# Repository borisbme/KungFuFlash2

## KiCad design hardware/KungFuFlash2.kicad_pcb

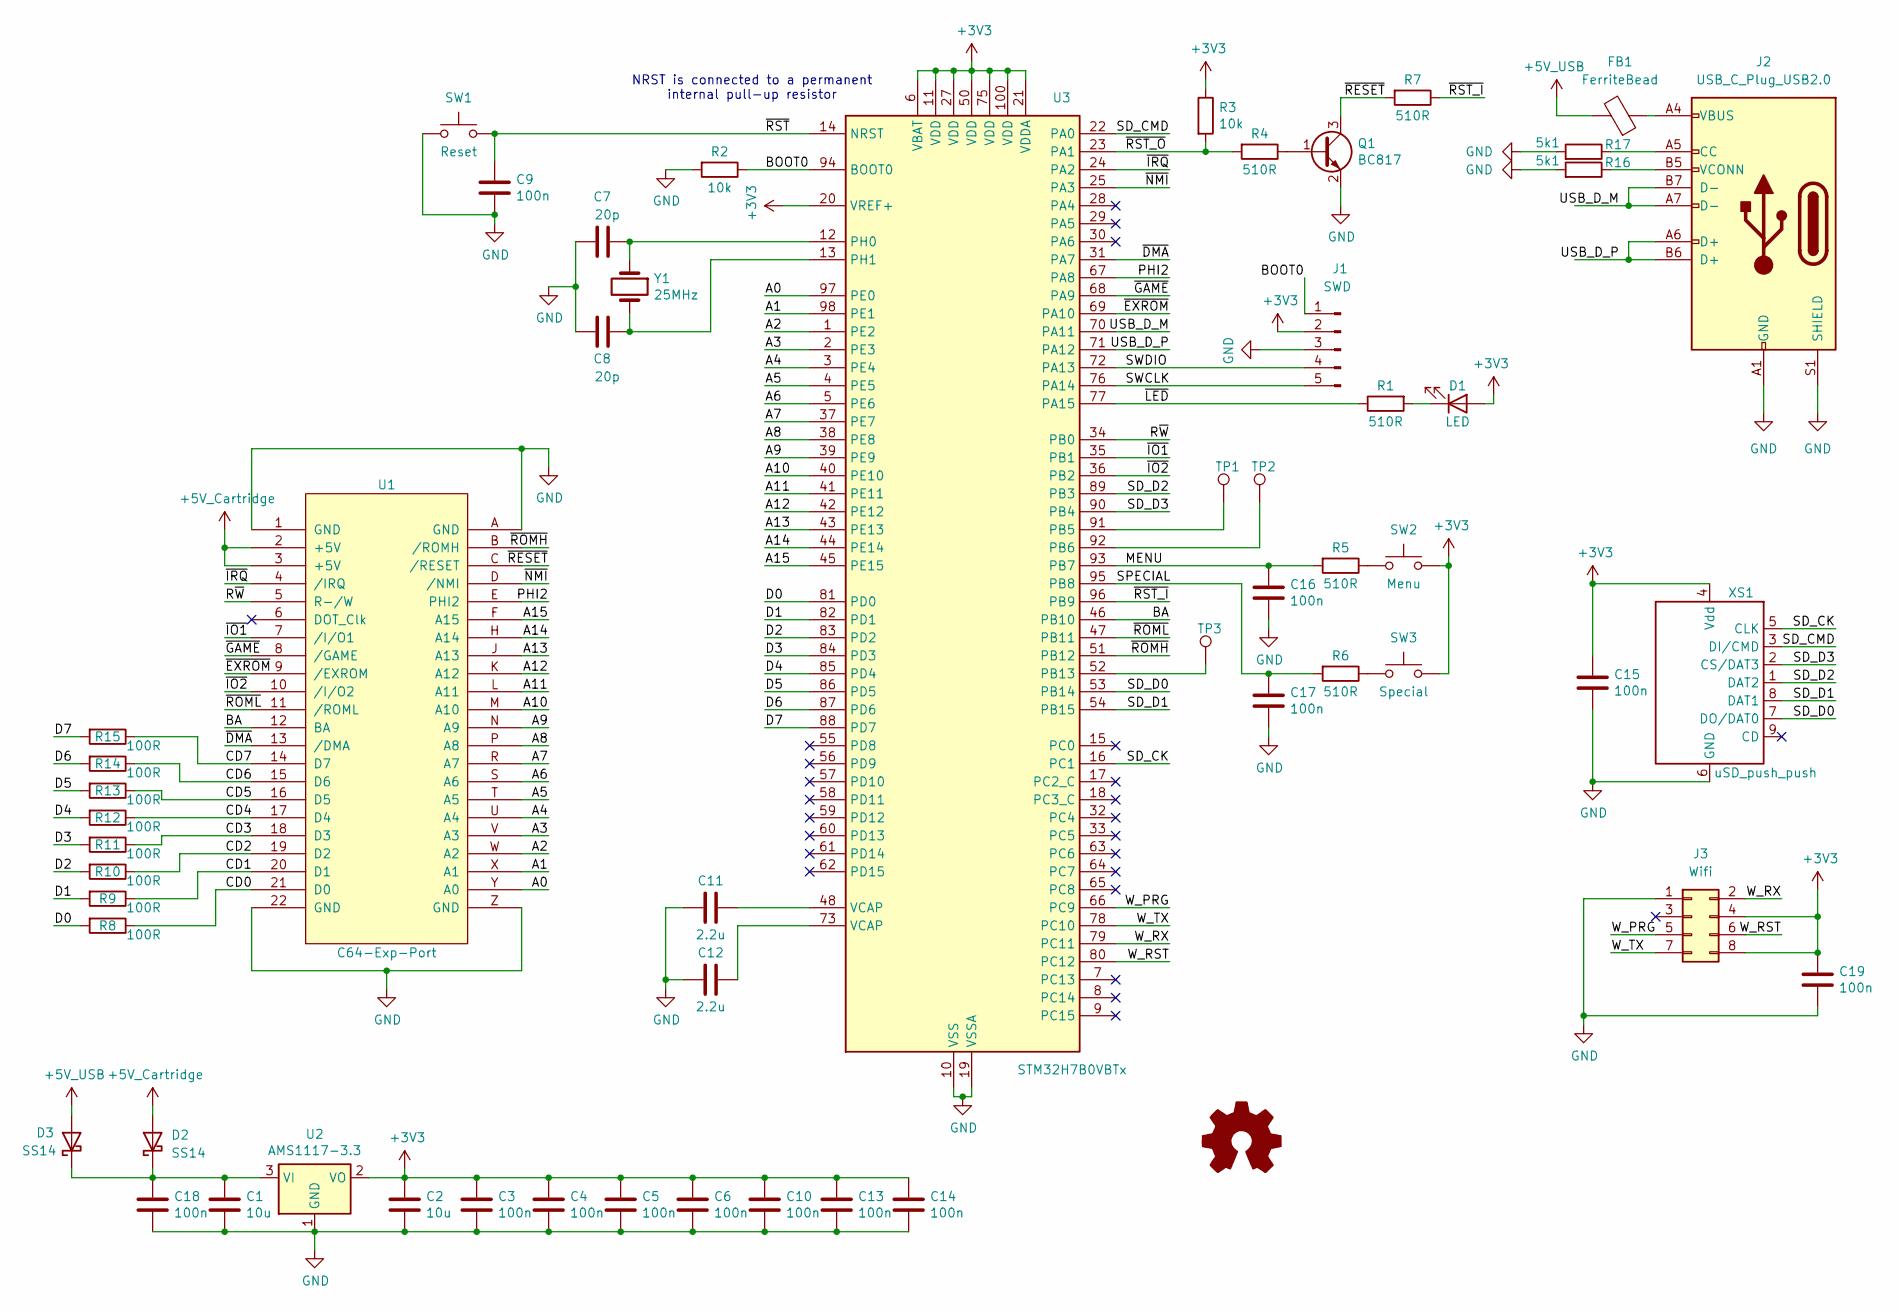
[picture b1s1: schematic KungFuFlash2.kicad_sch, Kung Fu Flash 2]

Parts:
C1, C2: 10u; C_0805_2012Metric_Pad1.18x1.45mm_HandSolder; LCSC C19702
C3, C4, C5, C6, C9, C10, C13, C14, C15, C16, C17, C18, C19: 100n; C_0603_1608Metric_Pad1.08x0.95mm_HandSolder; LCSC C38898
C7, C8: 20p; C_0603_1608Metric_Pad1.08x0.95mm_HandSolder; LCSC C105621
C11, C12: 2.2u; C_0805_2012Metric_Pad1.18x1.45mm_HandSolder; LCSC C19110
D1: LED; LED_0805_2012Metric_Pad1.15x1.40mm_HandSolder; LCSC C84256
D2, D3: SS14; D_SMA_Handsoldering; LCSC C2480
FB1: FerriteBead; L_0805_2012Metric_Pad1.15x1.40mm_HandSolder; LCSC C1015
J1: SWD; PinHeader_1x05_P2.54mm_Vertical; LCSC C492404
J2: USB_C_Plug_USB2.0; USB_C_Receptacle_GCT_USB4105-xx-A_16P_TopMnt_Horizontal; LCSC C165948
J3: Wifi; PinSocket_2x04_P2.54mm_Vertical; LCSC C18723055
Q1: BC817; SOT-23; LCSC C52801
R1, R4, R5, R6, R7: 510R; R_0805_2012Metric_Pad1.20x1.40mm_HandSolder; LCSC C17734
R2, R3: 10k; R_0805_2012Metric_Pad1.20x1.40mm_HandSolder; LCSC C17414
R8, R9, R10, R11, R12, R13, R14, R15: 100R; R_0805_2012Metric_Pad1.20x1.40mm_HandSolder; LCSC C17408
R16, R17: 5k1; R_0805_2012Metric_Pad1.20x1.40mm_HandSolder; LCSC C27834
SW1: Reset; SW_PUSH_6mm_H8mm; LCSC C285486
SW2: Menu; SW_PUSH_6mm_H8mm; LCSC C285486
SW3: Special; SW_PUSH_6mm_H8mm; LCSC C285486
TP1, TP2, TP3: TestPoint_Pad_1.0x1.0mm
U1: C64-Exp-Port; C64-Cart
U2: AMS1117-3.3; SOT-223-3_TabPin2; LCSC C347222
U3: STM32H7B0VBTx; LQFP-100_14x14mm_P0.5mm; LCSC C730227
XS1: uSD_push_push; Conn_uSDcard
Y1: 25MHz; Crystal_SMD_5032-2Pin_5.0x3.2mm; LCSC C251592

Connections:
+3V3: C2.1, C3.1, C4.1, C5.1, C6.1, C10.1, C13.1, C14.1, C15.1, C19.1, D1.2 (A), J1.2, J3.4, J3.8, R3.1, SW2.1, SW3.1, U2.2 (VO), U3.6 (VBAT), U3.11 (VDD), U3.20 (VREF+), U3.21 (VDDA), U3.27 (VDD), U3.50 (VDD), U3.75 (VDD), U3.100 (VDD), XS1.4 (Vdd)
+5V_Cartridge: D2.2 (A), U1.2 (+5V), U1.3 (+5V)
+5V_USB: D3.2 (A), FB1.2
/A0: U1.Y (A0), U3.97 (PE0)
/A1: U1.X (A1), U3.98 (PE1)
/A2: U1.W (A2), U3.1 (PE2)
/A3: U1.V (A3), U3.2 (PE3)
/A4: U1.U (A4), U3.3 (PE4)
/A5: U1.T (A5), U3.4 (PE5)
/A6: U1.S (A6), U3.5 (PE6)
/A7: U1.R (A7), U3.37 (PE7)
/A8: U1.P (A8), U3.38 (PE8)
/A9: U1.N (A9), U3.39 (PE9)
/A10: U1.M (A10), U3.40 (PE10)
/A11: U1.L (A11), U3.41 (PE11)
/A12: U1.K (A12), U3.42 (PE12)
/A13: U1.J (A13), U3.43 (PE13)
/A14: U1.H (A14), U3.44 (PE14)
/A15: U1.F (A15), U3.45 (PE15)
/BA: U1.12 (BA), U3.46 (PB10)
/BOOT0: J1.1, R2.1, U3.94 (BOOT0)
/CD0: R8.1, U1.21 (D0)
/CD1: R9.1, U1.20 (D1)
/CD2: R10.1, U1.19 (D2)
/CD3: R11.1, U1.18 (D3)
/CD4: R12.1, U1.17 (D4)
/CD5: R13.1, U1.16 (D5)
/CD6: R14.1, U1.15 (D6)
/CD7: R15.1, U1.14 (D7)
/D0: R8.2, U3.81 (PD0)
/D1: R9.2, U3.82 (PD1)
/D2: R10.2, U3.83 (PD2)
/D3: R11.2, U3.84 (PD3)
/D4: R12.2, U3.85 (PD4)
/D5: R13.2, U3.86 (PD5)
/D6: R14.2, U3.87 (PD6)
/D7: R15.2, U3.88 (PD7)
/MENU: C16.1, R5.2, U3.93 (PB7)
/PHI2: U1.E (PHI2), U3.67 (PA8)
/R~W: U1.5 (R-/W), U3.34 (PB0)
/SD_CK: U3.16 (PC1), XS1.5 (CLK)
/SD_CMD: U3.22 (PA0), XS1.3 (DI/CMD)
/SD_D0: U3.53 (PB14), XS1.7 (DO/DAT0)
/SD_D1: U3.54 (PB15), XS1.8 (DAT1)
/SD_D2: U3.89 (PB3), XS1.1 (DAT2)
/SD_D3: U3.90 (PB4), XS1.2 (CS/DAT3)
/SPECIAL: C17.1, R6.2, U3.95 (PB8)
/SWCLK: J1.5, U3.76 (PA14)
/SWDIO: J1.4, U3.72 (PA13)
/USB_D_M: J2.A7 (D-), J2.B7 (D-), U3.70 (PA11)
/USB_D_P: J2.A6 (D+), J2.B6 (D+), U3.71 (PA12)
/W_PRG: J3.5, U3.66 (PC9)
/W_RST: J3.6, U3.80 (PC12)
/W_RX: J3.2, U3.79 (PC11)
/W_TX: J3.7, U3.78 (PC10)
/~DMA: U1.13 (/DMA), U3.31 (PA7)
/~EXROM: U1.9 (/EXROM), U3.69 (PA10)
/~GAME: U1.8 (/GAME), U3.68 (PA9)
/~IO1: U1.7 (/I/O1), U3.35 (PB1)
/~IO2: U1.10 (/I/O2), U3.36 (PB2)
/~IRQ: U1.4 (/IRQ), U3.24 (PA2)
/~LED: R1.1, U3.77 (PA15)
/~NMI: U1.D (/NMI), U3.25 (PA3)
/~RESET: Q1.3 (C), R7.2, U1.C (/RESET)
/~ROMH: U1.B (/ROMH), U3.51 (PB12)
/~ROML: U1.11 (/ROML), U3.47 (PB11)
/~RST_I: R7.1, U3.96 (PB9)
/~RST_O: R3.2, R4.2, U3.23 (PA1)
/~RST: C9.1, SW1.2, U3.14 (NRST)
GND: C1.2, C2.2, C3.2, C4.2, C5.2, C6.2, C7.1, C8.1, C9.2, C10.2, C11.1, C12.2, C13.2, C14.2, C15.2, C16.2, C17.2, C18.2, C19.2, J1.3, J2.A1 (GND), J2.A12 (GND), J2.B1 (GND), J2.B12 (GND), J2.S1 (SHIELD), J3.1, Q1.2 (E), R2.2, R16.2, R17.2, SW1.1, U1.1 (GND), U1.22 (GND), U1.A (GND), U1.Z (GND), U2.1 (GND), U3.10 (VSS), U3.19 (VSSA), U3.26 (VSS), U3.49 (VSS), U3.74 (VSS), U3.99 (VSS), XS1.6 (GND)
unnamed: C11.2, U3.48 (VCAP)
unnamed: C12.1, U3.73 (VCAP)
unnamed: D1.1 (K), R1.2
unnamed: C1.1, C18.1, D2.1 (K), D3.1 (K), U2.3 (VI)
unnamed: FB1.1, J2.A4 (VBUS), J2.A9 (VBUS), J2.B4 (VBUS), J2.B9 (VBUS)
unnamed: J2.A5 (CC), R17.1
unnamed: J2.B5 (VCONN), R16.1
unnamed: Q1.1 (B), R4.1
unnamed: R5.1, SW2.2
unnamed: R6.1, SW3.2
unnamed: TP1.1, U3.91 (PB5)
unnamed: TP2.1, U3.92 (PB6)
unnamed: TP3.1, U3.52 (PB13)
unnamed: C7.2, U3.12 (PH0), Y1.1
unnamed: C8.2, U3.13 (PH1), Y1.2

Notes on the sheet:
NRST is connected to a permanent internal pull-up resistor

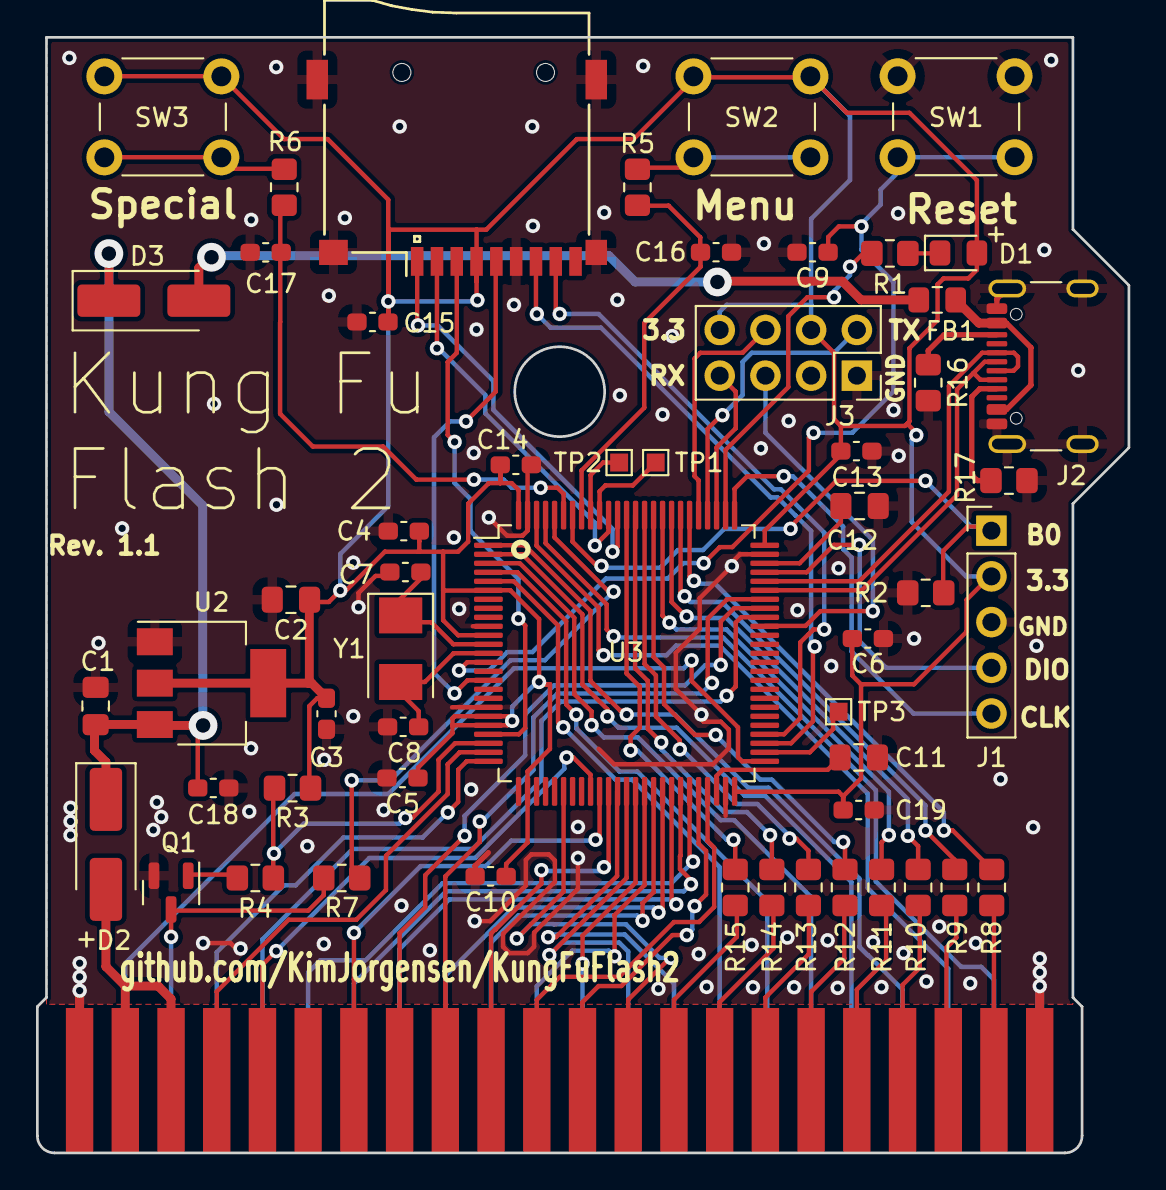
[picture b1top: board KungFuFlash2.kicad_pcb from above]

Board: 2 copper layers, 60.6 x 62.0 mm, 55 parts (0 on the bottom side), 85 nets.

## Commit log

2025-01-03 added USB-C connector
